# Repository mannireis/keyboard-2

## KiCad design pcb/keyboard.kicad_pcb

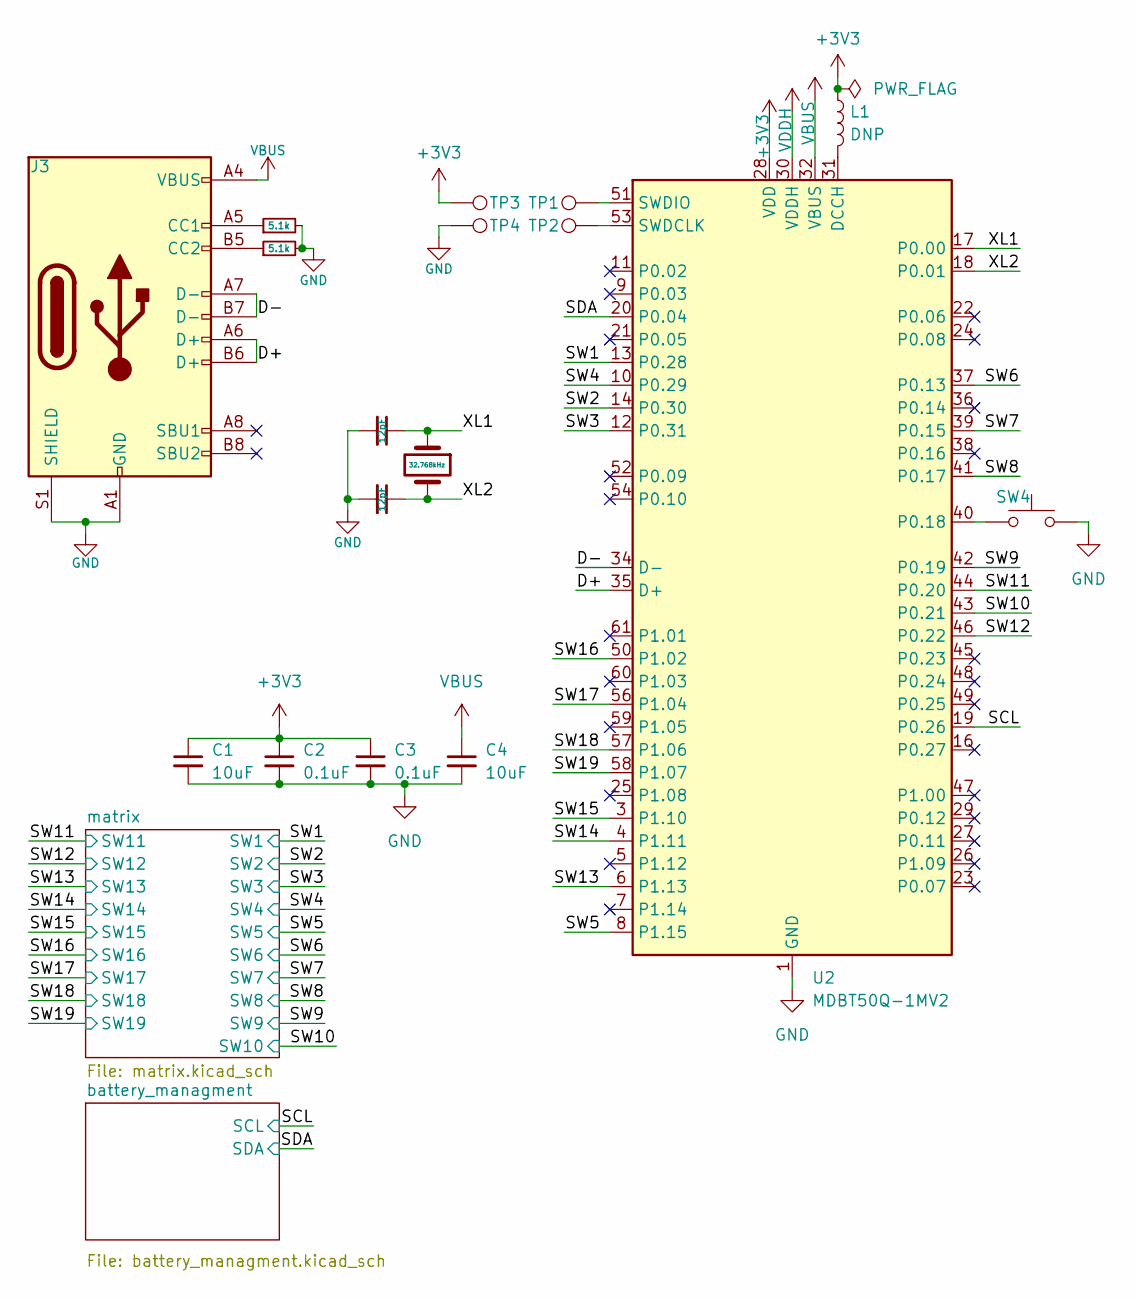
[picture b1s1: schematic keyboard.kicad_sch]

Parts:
C1, C4: 10uF; C_0402_1005Metric
C2, C3: 0.1uF; C_0402_1005Metric
C14, C15: 12pF; C_0402_1005Metric
J3: USB_C_Receptacle_USB2.0_16P; USB_C_Receptacle_HRO_TYPE-C-31-M-12
L1: DNP; L_0402_1005Metric
R1, R2: 5.1k; C_0402_1005Metric
SW4: SW_Push; SW_Push_1P1T_NO_CK_KMR2
TP1, TP2, TP3, TP4: TestPoint; TestPoint_Pad_3.0x3.0mm
U2: MDBT50Q-1MV2; Raytac_MDBT50Q
Y2: 32.768kHz; Crystal_SMD_3215-2Pin_3.2x1.5mm

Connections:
+3V3: C1.1, C2.1, C3.1, L1.1, TP3.1, U2.28 (VDD); also elsewhere on the board
/D+: J3.A6 (D+), J3.B6 (D+), U2.35 (D+)
/D-: J3.A7 (D-), J3.B7 (D-), U2.34 (D-)
/SCL: U2.19 (P0.26); also elsewhere on the board
/SDA: U2.20 (P0.04); also elsewhere on the board
/SW1: U2.13 (P0.28); also elsewhere on the board
/SW2: U2.14 (P0.30); also elsewhere on the board
/SW3: U2.12 (P0.31); also elsewhere on the board
/SW4: U2.10 (P0.29); also elsewhere on the board
/SW5: U2.8 (P1.15); also elsewhere on the board
/SW6: U2.37 (P0.13); also elsewhere on the board
/SW7: U2.39 (P0.15); also elsewhere on the board
/SW8: U2.41 (P0.17); also elsewhere on the board
/SW9: U2.42 (P0.19); also elsewhere on the board
/SW10: U2.43 (P0.21); also elsewhere on the board
/SW11: U2.44 (P0.20); also elsewhere on the board
/SW12: U2.46 (P0.22); also elsewhere on the board
/SW13: U2.6 (P1.13); also elsewhere on the board
/SW14: U2.4 (P1.11); also elsewhere on the board
/SW15: U2.3 (P1.10); also elsewhere on the board
/SW16: U2.50 (P1.02); also elsewhere on the board
/SW17: U2.56 (P1.04); also elsewhere on the board
/SW18: U2.57 (P1.06); also elsewhere on the board
/SW19: U2.58 (P1.07); also elsewhere on the board
/XL1: C15.1, U2.17 (P0.00), Y2.1
/XL2: C14.1, U2.18 (P0.01), Y2.2
GND: C1.2, C2.2, C3.2, C4.2, C14.2, C15.2, J3.A1 (GND), J3.A12 (GND), J3.B1 (GND), J3.B12 (GND), J3.S1 (SHIELD), R1.2, R2.2, SW4.2, TP4.1, U2.1 (GND), U2.2 (GND), U2.15 (GND), U2.33 (GND), U2.55 (GND); also elsewhere on the board
unnamed: J3.A5 (CC1), R2.1
unnamed: J3.B5 (CC2), R1.1
unnamed: L1.2, U2.31 (DCCH)
unnamed: SW4.1, U2.40 (P0.18)
unnamed: TP2.1, U2.53 (SWDCLK)
unnamed: TP1.1, U2.51 (SWDIO)
VBUS: C4.1, J3.A4 (VBUS), J3.A9 (VBUS), J3.B4 (VBUS), J3.B9 (VBUS), U2.32 (VBUS); also elsewhere on the board
VDDH: U2.30 (VDDH); also elsewhere on the board

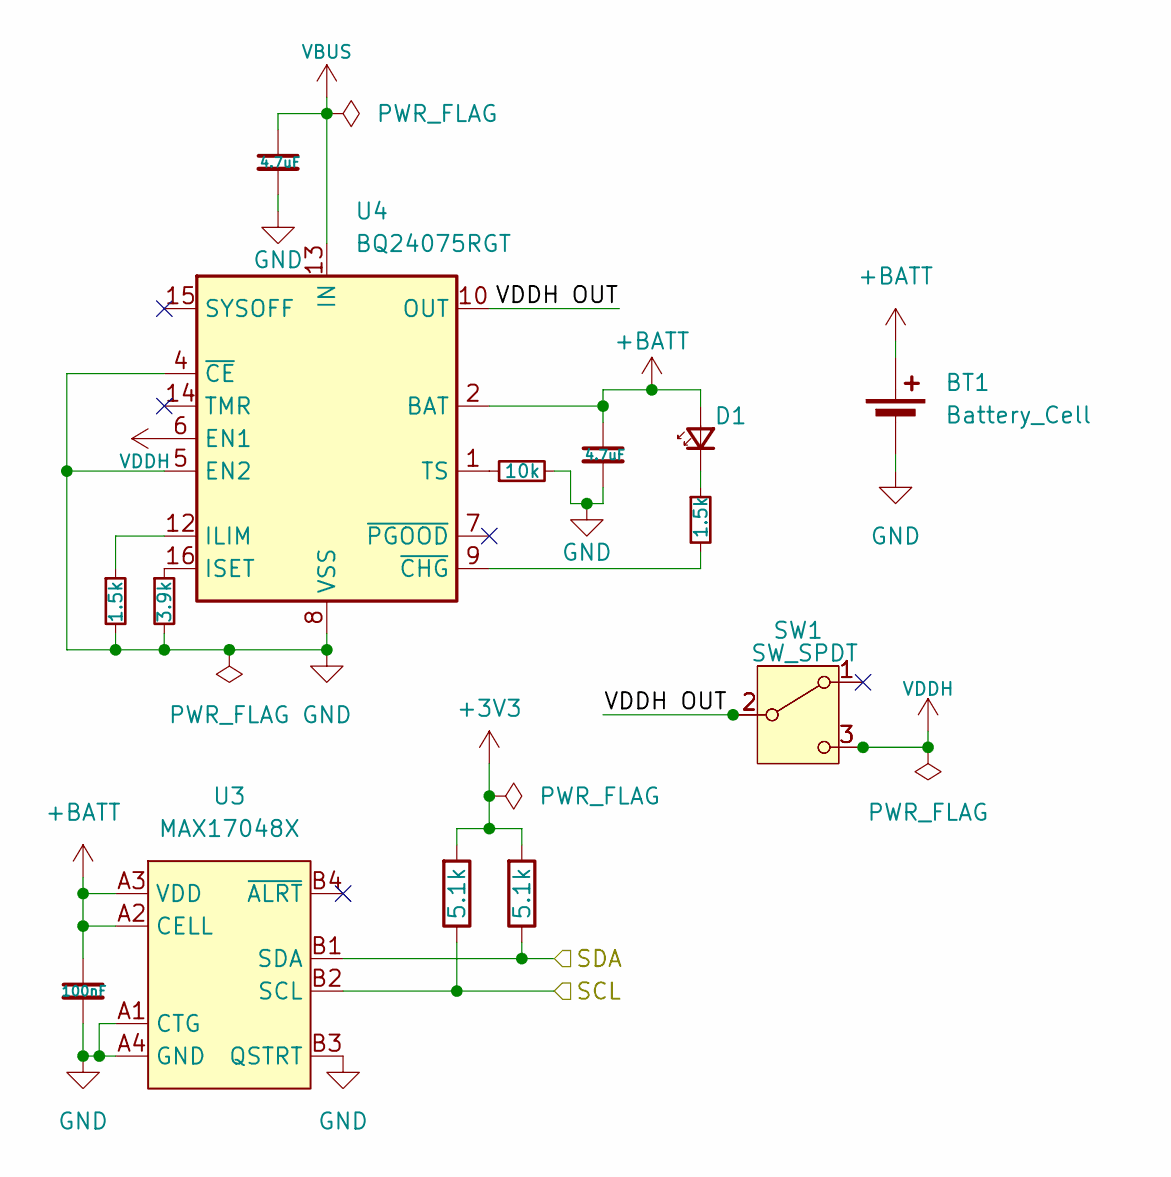
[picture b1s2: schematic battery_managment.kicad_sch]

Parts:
BT1: Battery_Cell; PinHeader_1x02_P2.00mm_Vertical
C16, C17: 4.7uF; C_0402_1005Metric
C18: 100nF; C_0402_1005Metric
D1: LED_Small; LED_0603_1608Metric
R3, R6: 1.5k; C_0402_1005Metric
R4: 3.9k; C_0402_1005Metric
R5: 10k; C_0402_1005Metric
R15, R16: 5.1k; C_0402_1005Metric; LCSC Part # C25905
SW1, SW2: SW_SPDT; SW_SPDT_Shouhan_MSK12C02
U3: MAX17048X; WLP-8_1.67x0.93_P0.4
U4: BQ24075RGT; VQFN-16-1EP_3x3mm_P0.5mm_EP1.6x1.6mm

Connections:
+3V3: R15.2, R16.2; also elsewhere on the board
+BATT: BT1.1 (+), C17.1, C18.1, D1.2 (A), U3.A2 (CELL), U3.A3 (VDD), U4.2 (BAT), U4.3 (BAT)
/SCL: R15.1, U3.B2 (SCL); also elsewhere on the board
/SDA: R16.1, U3.B1 (SDA); also elsewhere on the board
/battery_managment/VDDH OUT: SW1.2 (B), SW2.2 (B), U4.10 (OUT), U4.11 (OUT)
GND: BT1.2 (-), C16.2, C17.2, C18.2, R3.2, R4.2, R5.2, U3.A1 (CTG), U3.A4 (GND), U3.B3 (QSTRT), U4.4 (~CE), U4.5 (EN2), U4.8 (VSS), U4.17 (VSS); also elsewhere on the board
unnamed: D1.1 (K), R6.1
unnamed: R3.1, U4.12 (ILIM)
unnamed: R4.1, U4.16 (ISET)
unnamed: R5.1, U4.1 (TS)
unnamed: R6.2, U4.9 (~CHG)
VBUS: C16.1, U4.13 (IN); also elsewhere on the board
VDDH: SW1.3 (C), SW2.3 (C), U4.6 (EN1); also elsewhere on the board

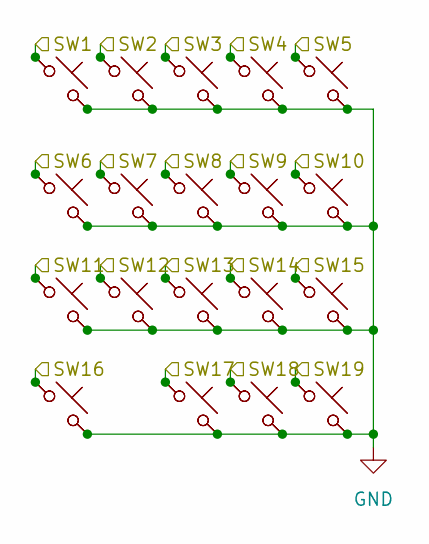
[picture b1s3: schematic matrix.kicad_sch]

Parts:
SW3, SW5, SW6, SW7, SW8, SW9, SW10, SW11, SW12, SW13, SW14, SW15, SW16, SW17, SW18, SW19, SW20, SW21, SW22, SW23, SW24, SW25, SW26, SW27, SW28, SW29, SW30, SW31, SW32, SW33, SW34, SW35, SW36, SW37, SW38, SW39, SW40, SW41: SW_Push_45deg; choc_v2_swap

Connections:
/SW1: SW3.1, SW23.1; also elsewhere on the board
/SW2: SW5.1, SW27.1; also elsewhere on the board
/SW3: SW6.1, SW30.1; also elsewhere on the board
/SW4: SW7.1, SW34.1; also elsewhere on the board
/SW5: SW8.1, SW38.1; also elsewhere on the board
/SW6: SW9.1, SW24.1; also elsewhere on the board
/SW7: SW10.1, SW28.1; also elsewhere on the board
/SW8: SW11.1, SW31.1; also elsewhere on the board
/SW9: SW12.1, SW35.1; also elsewhere on the board
/SW10: SW13.1, SW39.1; also elsewhere on the board
/SW11: SW14.1, SW25.1; also elsewhere on the board
/SW12: SW15.1, SW29.1; also elsewhere on the board
/SW13: SW16.1, SW32.1; also elsewhere on the board
/SW14: SW17.1, SW36.1; also elsewhere on the board
/SW15: SW18.1, SW40.1; also elsewhere on the board
/SW16: SW19.1, SW26.1; also elsewhere on the board
/SW17: SW20.1, SW33.1; also elsewhere on the board
/SW18: SW21.1, SW37.1; also elsewhere on the board
/SW19: SW22.1, SW41.1; also elsewhere on the board
GND: SW3.2, SW5.2, SW6.2, SW7.2, SW8.2, SW9.2, SW10.2, SW11.2, SW12.2, SW13.2, SW14.2, SW15.2, SW16.2, SW17.2, SW18.2, SW19.2, SW20.2, SW21.2, SW22.2, SW23.2, SW24.2, SW25.2, SW26.2, SW27.2, SW28.2, SW29.2, SW30.2, SW31.2, SW32.2, SW33.2, SW34.2, SW35.2, SW36.2, SW37.2, SW38.2, SW39.2, SW40.2, SW41.2; also elsewhere on the board

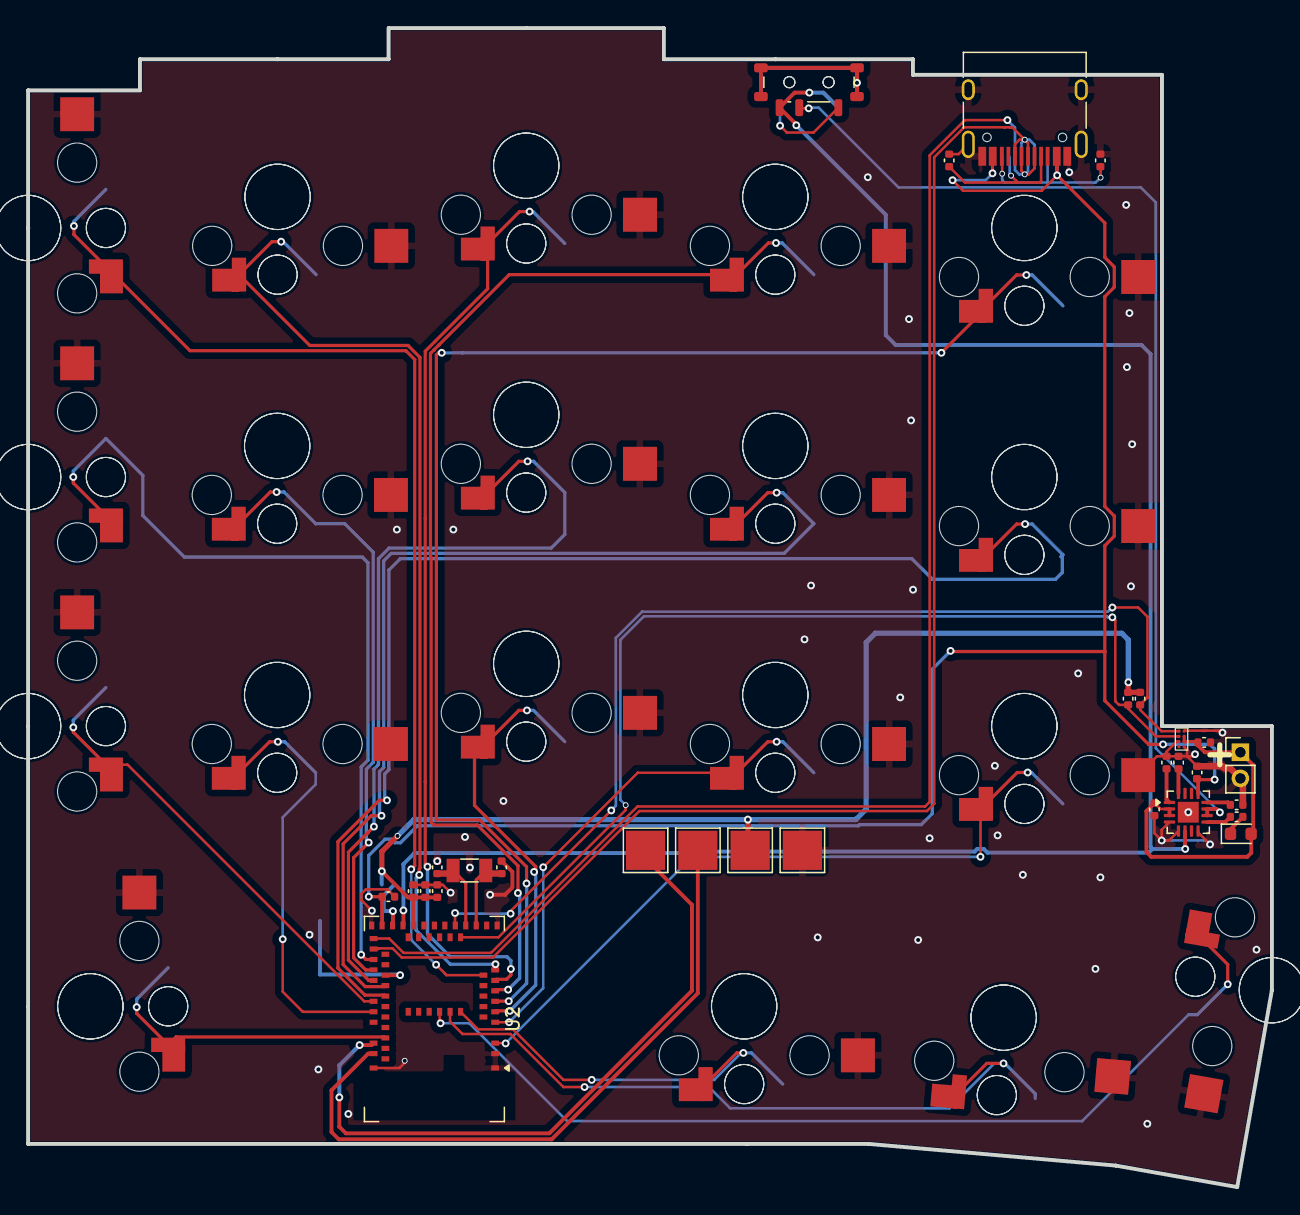
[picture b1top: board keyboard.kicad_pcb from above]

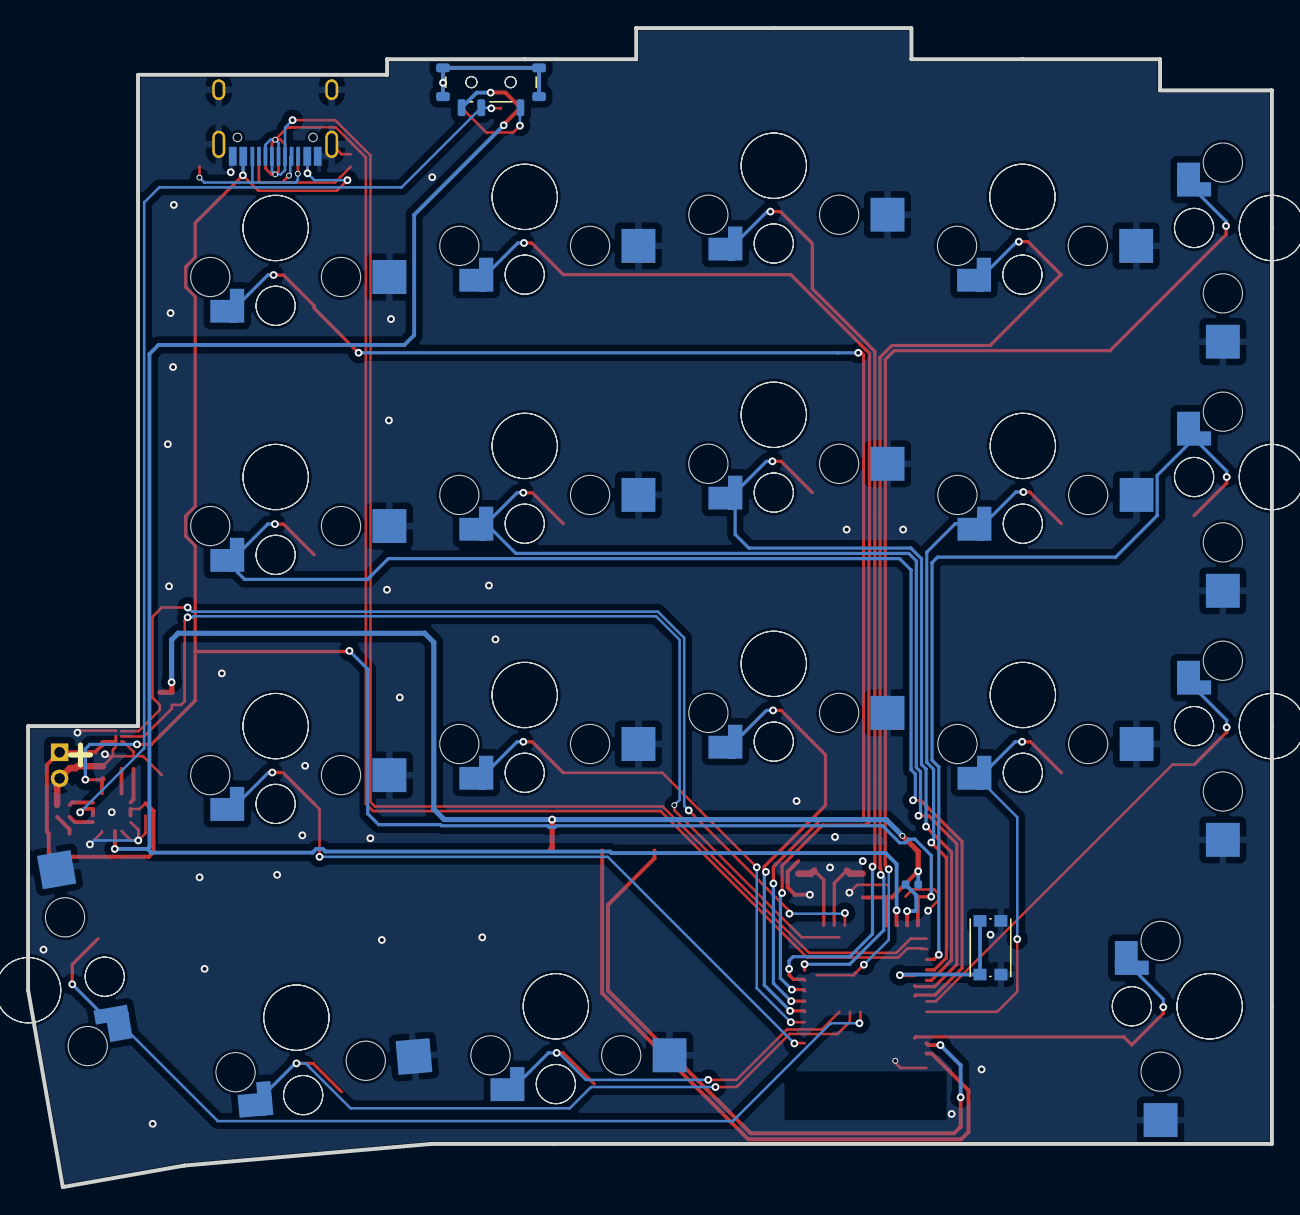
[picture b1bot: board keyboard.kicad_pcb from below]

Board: 2 copper layers, 95.1 x 88.6 mm, 70 parts (22 on the bottom side), 42 nets.

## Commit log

2026-01-17 Add greeting to README file
2026-01-17 add pcb
